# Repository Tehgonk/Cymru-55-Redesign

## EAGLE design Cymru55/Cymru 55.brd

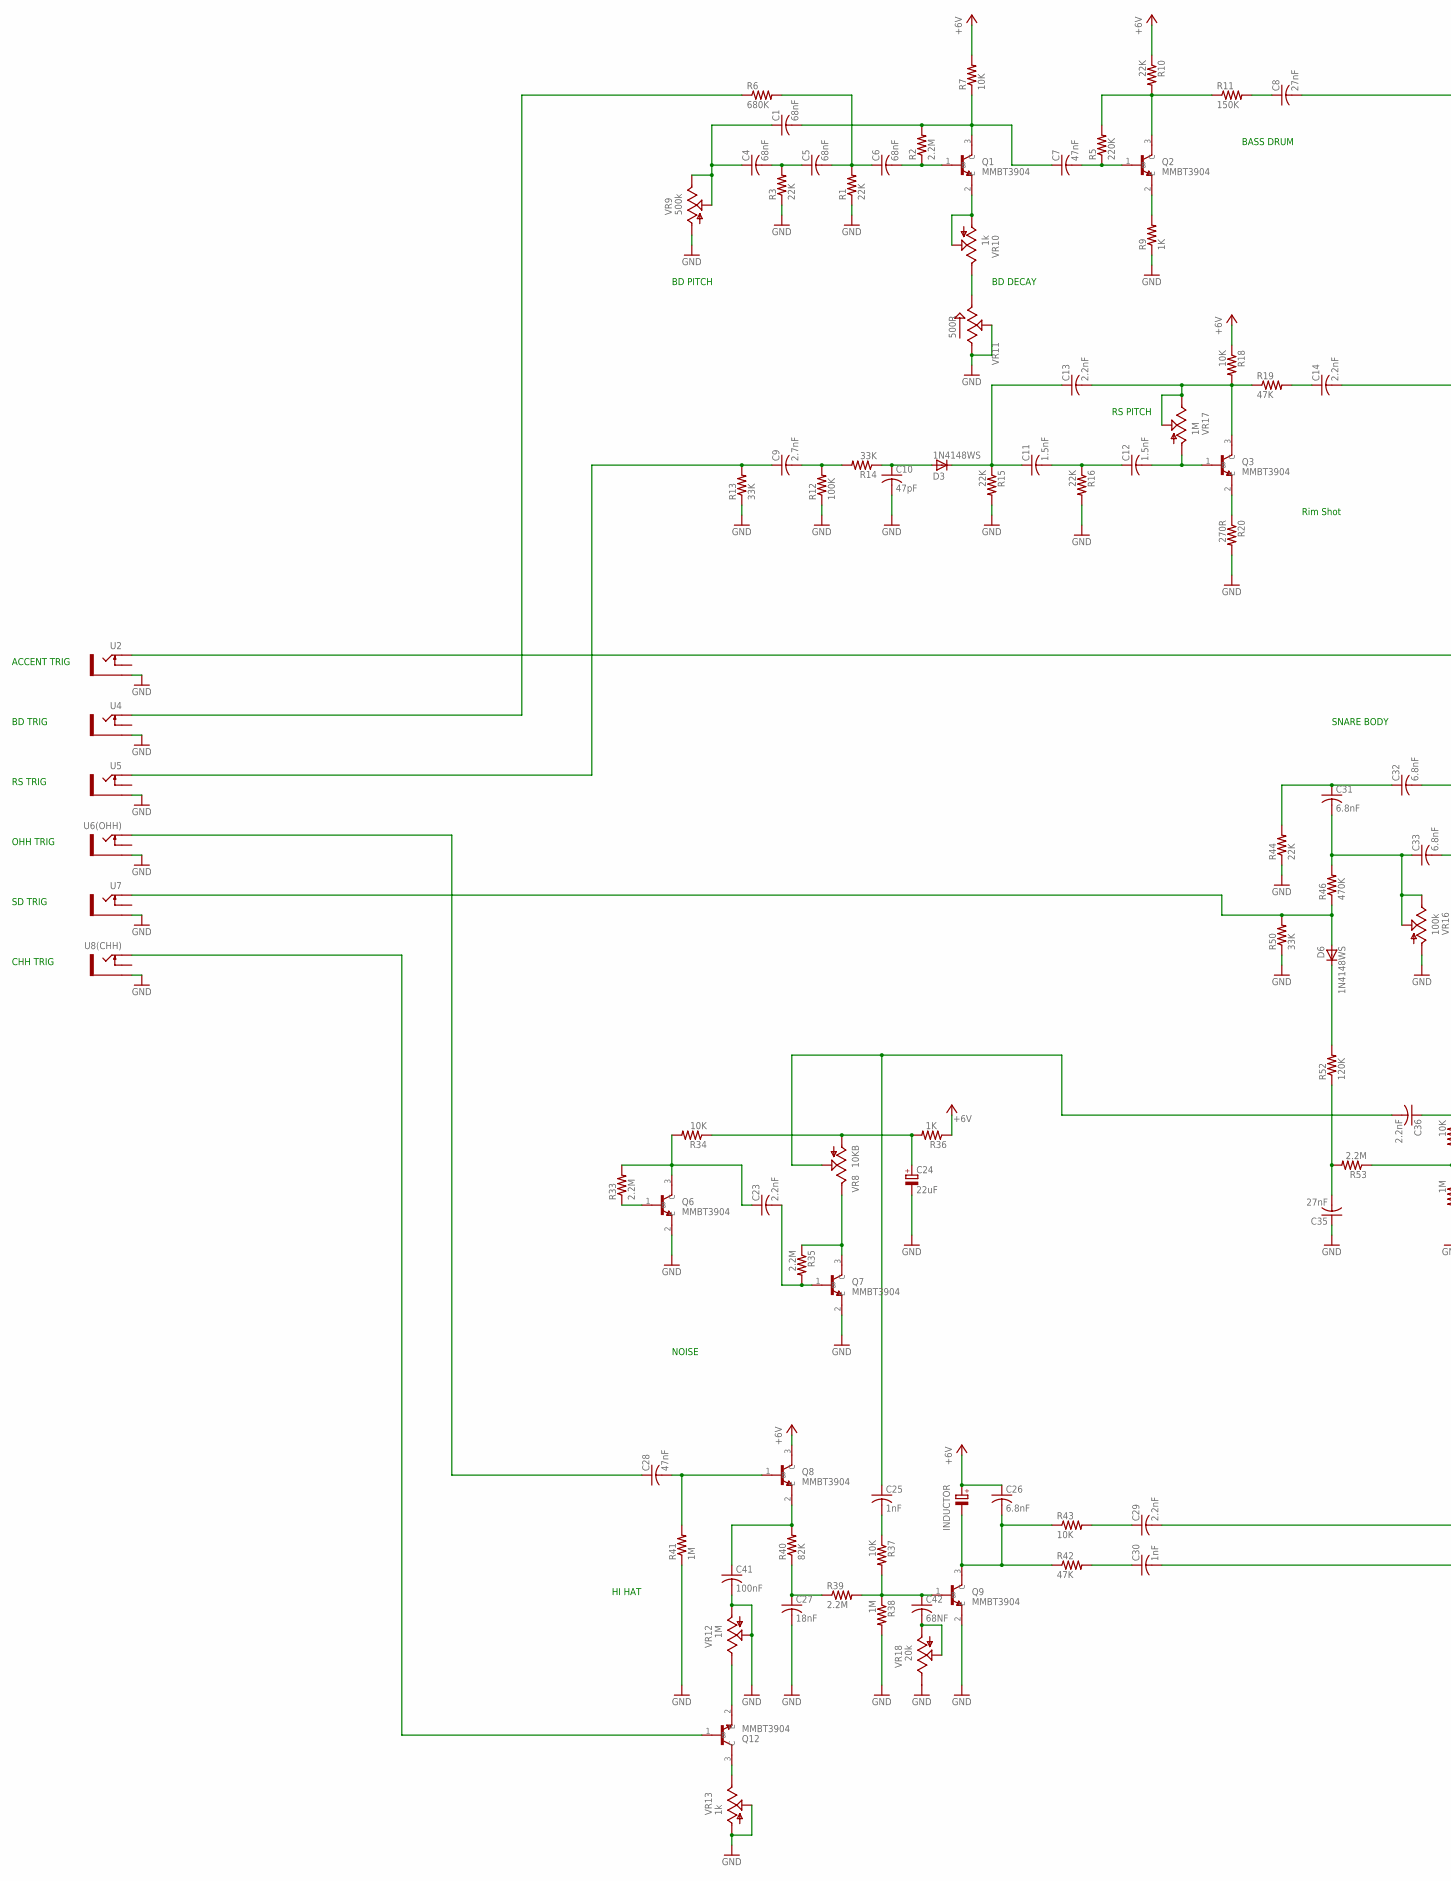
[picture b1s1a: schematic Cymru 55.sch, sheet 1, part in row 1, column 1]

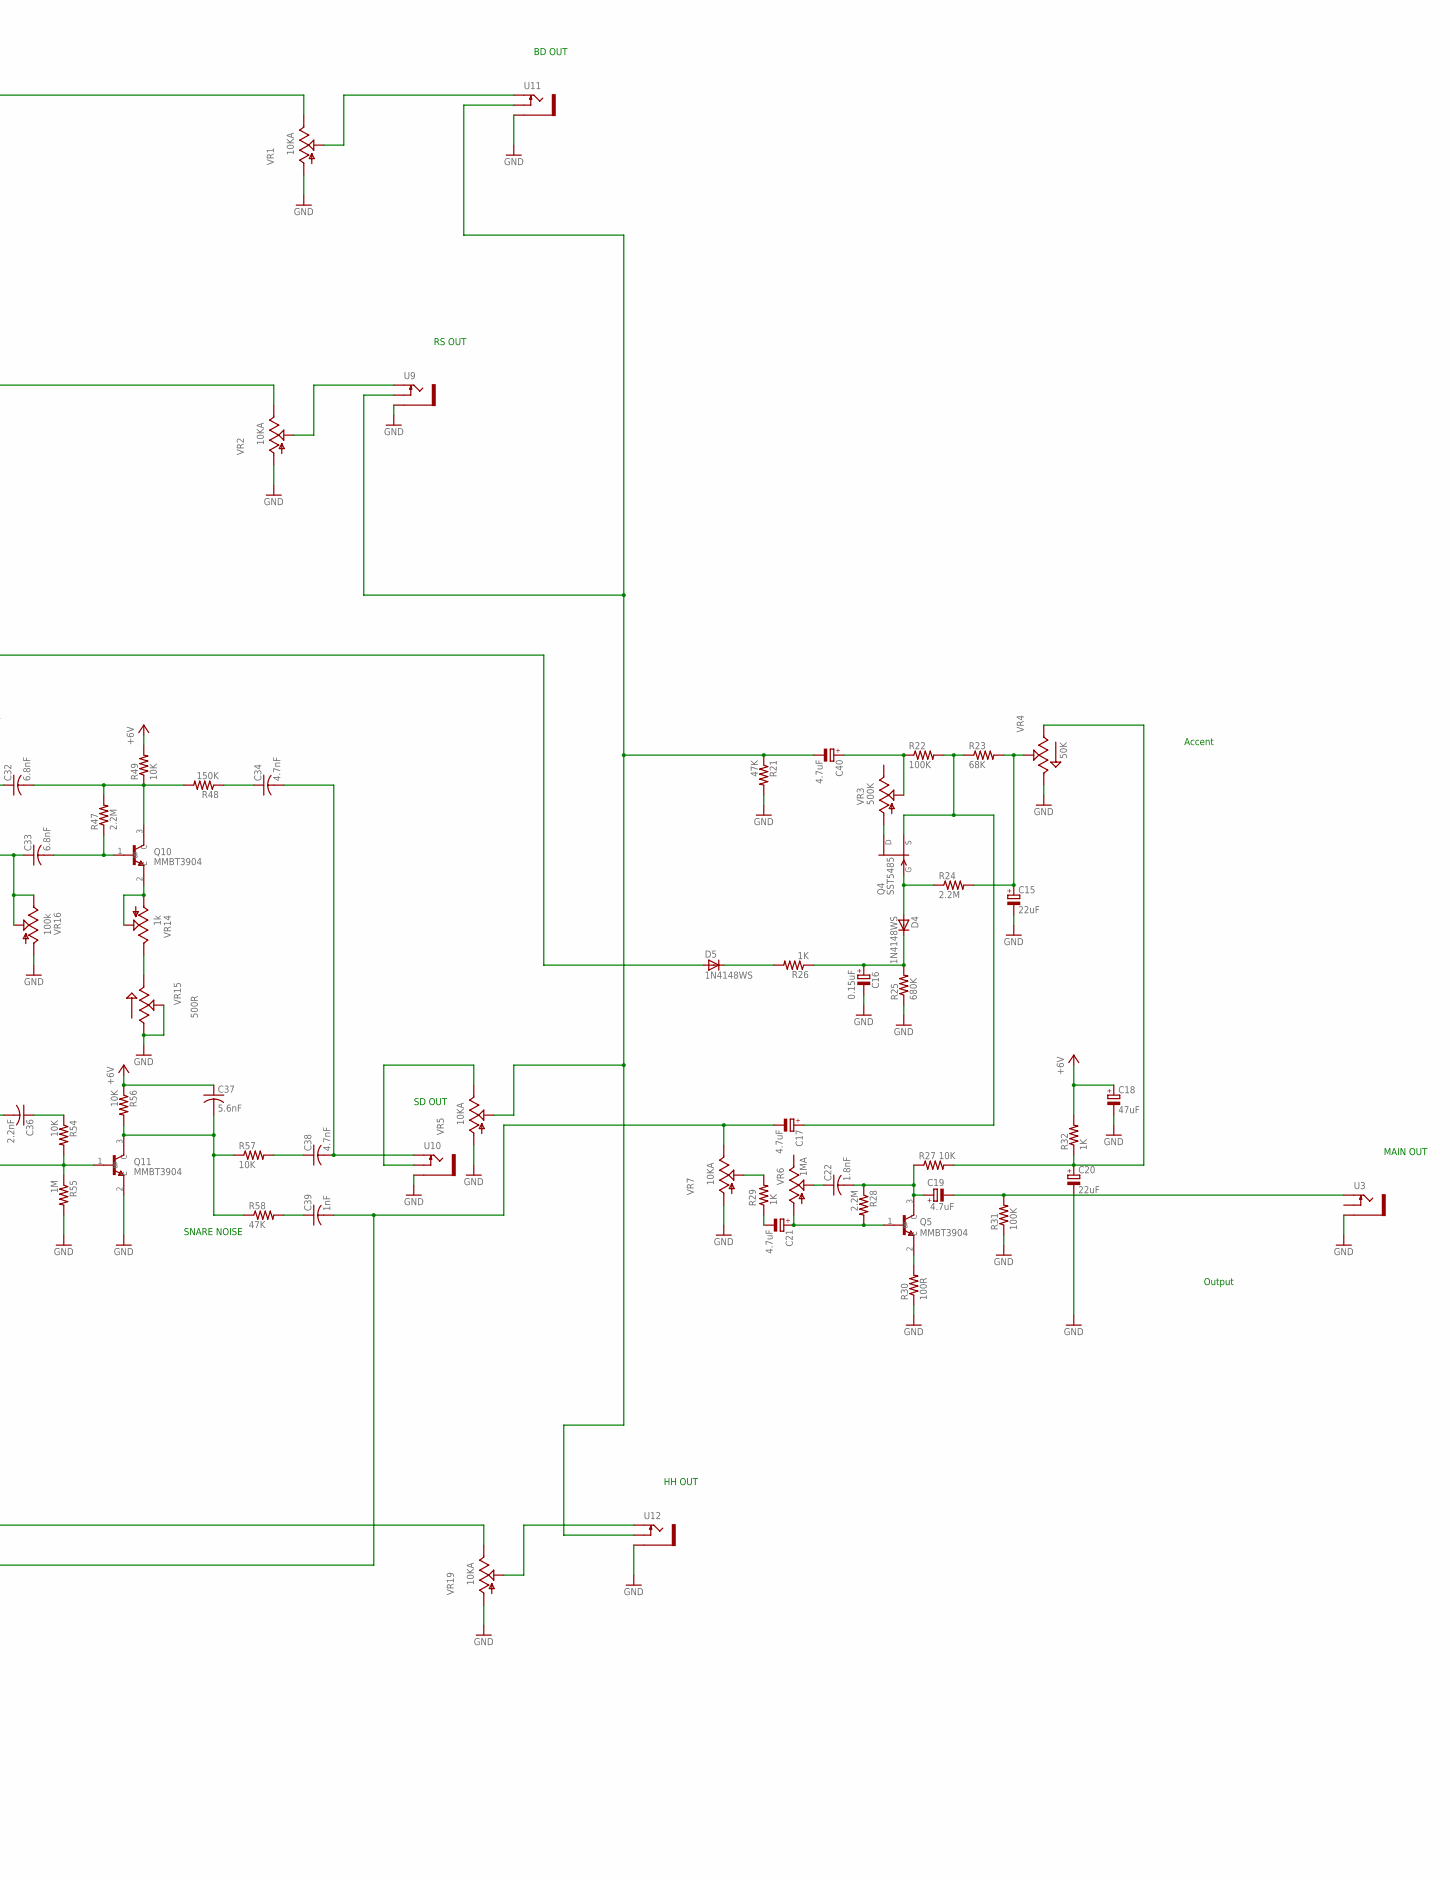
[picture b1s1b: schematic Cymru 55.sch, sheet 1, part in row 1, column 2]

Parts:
C1, C4, C5, C6: 68nF; C0603
C7, C28: 47nF; C0603
C8, C35: 27nF; C0603
C9: 2.7nF; C0603
C10: 47pF; C0603
C11, C12: 1.5nF; C0603
C13, C14, C23, C29, C36: 2.2nF; C0603
C15, C20, C24: 22uF; E2,5RE
C16: 0.15uF; E2,5RE
C17, C19, C21, C40: 4.7uF; E2,5RE
C18: 47uF; E2,5RE
C22: 1.8nF; C0603
C25, C30, C39: 1nF; C0603
C26, C31, C32, C33: 6.8nF; C0603
C27: 18nF; C0603
C34, C38: 4.7nF; C0603
C37: 5.6nF; C0603
C41: 100nF; C0603
C42: 68NF; C0603
D3, D4, D5, D6: 1N4148WS; SOD323
INDUCTOR: 47MH; E2,5RE
Q1, Q2, Q3, Q5, Q6, Q7, Q8, Q9, Q10, Q11, Q12: MMBT3904; SOT95P240X120-3N
Q4: SST5485; SOT23
R1, R3, R10, R15, R16, R44: 22K; R0603
R2, R24, R28, R33, R35, R39, R47, R53: 2.2M; R0603
R5: 220K; R0603
R6, R25: 680K; R0603
R7, R18, R27, R34, R37, R43, R49, R54, R56, R57: 10K; R0603
R9, R26, R29, R32, R36: 1K; R0603
R11, R48: 150K; R0603
R12, R22, R31: 100K; R0603
R13, R14, R50: 33K; R0603
R19, R21, R42, R58: 47K; R0603
R20: 270R; R0603
R23: 68K; R0603
R30: 100R; R0603
R38, R41, R55: 1M; R0603
R40: 82K; R0603
R46: 470K; R0603
R52: 120K; R0603
U2, U3, U4, U5, U6(OHH), U7, U8(CHH), U9, U10, U11, U12: THONKICONNNEW; WQP-PJ301M-12_JACK
VR1, VR2, VR5, VR7, VR19: 10KA; 9MM_SNAP-IN_POT
VR3: 500K; 9MM_SNAP-IN_POT
VR4: 50K; TRIM_3296W-1-250LF
VR6: 1MA; 9MM_SNAP-IN_POT
VR8: 10KB; 9MM_SNAP-IN_POT
VR9: 500k; 9MM_SNAP-IN_POT
VR10, VR13, VR14: 1k; 9MM_SNAP-IN_POT
VR11, VR15: 500R; TRIM_3296W-1-250LF
VR12, VR17: 1M; 9MM_SNAP-IN_POT
VR16: 100k; 9MM_SNAP-IN_POT
VR18: 20k; 9MM_SNAP-IN_POT

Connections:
+5V: C18.+, C26.1, C37.1, INDUCTOR.+, Q8.3 (C), R7.2, R10.1, R18.1, R32.2, R36.1, R49.2, R56.1; also elsewhere on the board
GND: C10.2, C15.-, C16.-, C18.-, C20.-, C24.-, C27.2, C35.1, C41.2, Q6.2 (E), Q7.2 (E), Q9.2 (E), Q11.2 (E), R1.1, R3.1, R9.1, R12.1, R13.1, R15.2, R16.2, R20.2, R21.2, R25.1, R30.1, R31.1, R38.2, R41.1, R44.1, R50.1, R55.2, U2.P$3_SLEEVE (SLEEVE), U3.P$3_SLEEVE (SLEEVE), U4.P$3_SLEEVE (SLEEVE), U5.P$3_SLEEVE (SLEEVE), U6(OHH).P$3_SLEEVE (SLEEVE), U7.P$3_SLEEVE (SLEEVE), U8(CHH).P$3_SLEEVE (SLEEVE), U9.P$3_SLEEVE (SLEEVE), U10.P$3_SLEEVE (SLEEVE), U11.P$3_SLEEVE (SLEEVE), U12.P$3_SLEEVE (SLEEVE), VR1.1 (A), VR2.1 (A), VR4.3 (CW), VR5.1 (A), VR7.1 (A), VR9.1 (A), VR11.1 (CCW), VR11.2 (WIPER), VR12.1 (A), VR12.2 (S), VR13.1 (A), VR13.2 (S), VR15.1 (CCW), VR15.2 (WIPER), VR16.1 (A), VR18.3 (E), VR19.1 (A); also elsewhere on the board
unnamed: U10.P$2_SWITCH (SWITCH), VR5.3 (E)
unnamed: C1.1, C4.1, VR9.2 (S), VR9.3 (E)
unnamed: C1.2, C7.1, Q1.3 (C), R2.2, R7.1
unnamed: C6.2, Q1.1 (B), R2.1
unnamed: C5.2, C6.1, R1.2, R6.2
unnamed: C4.2, C5.1, R3.2
unnamed: Q3.2 (E), R20.1
unnamed: C9.2, R12.2, R14.2
unnamed: Q1.2 (E), VR10.1 (A), VR10.2 (S)
unnamed: C10.1, D3.A, R14.1
unnamed: C7.2, Q2.1 (B), R5.1
unnamed: Q2.3 (C), R5.2, R10.2, R11.1
unnamed: Q2.2 (E), R9.2
unnamed: C8.1, R11.2
unnamed: C11.1, C13.1, D3.C, R15.1
unnamed: C11.2, C12.1, R16.1
unnamed: C9.1, R13.2, U5.P$1_TIP (TIP)
unnamed: D4.A, Q4.3 (G), R24.1
unnamed: C16.+, D4.C, R25.2, R26.1
unnamed: C12.2, Q3.1 (B), VR17.1 (A)
unnamed: C14.2, VR2.3 (E)
unnamed: C14.1, R19.2
unnamed: Q4.1 (D), VR3.1 (A)
unnamed: C40.+, R22.1, VR3.2 (S)
unnamed: C21.-, R29.1
unnamed: C17.-, C30.2, C39.2, VR7.3 (E)
unnamed: C15.+, R23.2, R24.2, VR4.2 (WIPER)
unnamed: C17.+, Q4.2 (S), R22.2, R23.1
unnamed: R29.2, VR7.2 (S)
unnamed: C21.+, Q5.1 (B), R28.2, VR6.1 (A)
unnamed: C22.1, VR6.2 (S)
unnamed: C19.-, R31.2, U3.P$1_TIP (TIP)
unnamed: Q6.1 (B), R33.1
unnamed: C20.+, R27.2, R32.1, VR4.1 (CCW)
unnamed: Q5.2 (E), R30.2
unnamed: C23.1, Q6.3 (C), R33.2, R34.2
unnamed: C25.1, C36.2, VR8.2 (S)
unnamed: C23.2, Q7.1 (B), R35.2
unnamed: Q7.3 (C), R35.1, VR8.3 (E)
unnamed: C24.+, R34.1, R36.2, VR8.1 (A)
unnamed: C25.2, R37.1
unnamed: C42.2, VR18.1 (A), VR18.2 (S)
unnamed: C27.1, R39.1, R40.1
unnamed: C41.1, Q8.2 (E), R40.2
unnamed: C26.2, INDUCTOR.-, Q9.3 (C), R42.1, R43.1
unnamed: C28.2, Q8.1 (B), R41.2
unnamed: C29.1, R43.2
unnamed: C30.1, R42.2
unnamed: D5.C, R26.2
unnamed: C31.1, C32.1, R44.2
unnamed: C13.2, Q3.3 (C), R18.2, R19.1, VR17.2 (S), VR17.3 (E)
unnamed: C32.2, Q10.3 (C), R47.2, R48.2, R49.1
unnamed: C34.1, R48.1
unnamed: C33.2, Q10.1 (B), R47.1
unnamed: C31.2, C33.1, R46.2, VR16.2 (S), VR16.3 (E)
unnamed: C8.2, VR1.3 (E)
unnamed: D6.C, R52.2
unnamed: C35.2, R52.1, R53.2
unnamed: Q11.1 (B), R53.1, R54.2, R55.1
unnamed: C36.1, R54.1
unnamed: C37.2, Q11.3 (C), R56.2, R57.1, R58.1
unnamed: R6.1, U4.P$1_TIP (TIP)
unnamed: C39.1, R58.2
unnamed: C38.1, R57.2
unnamed: D5.A, U2.P$1_TIP (TIP)
unnamed: C28.1, U6(OHH).P$1_TIP (TIP)
unnamed: D6.A, R46.1, R50.2, U7.P$1_TIP (TIP)
unnamed: VR10.3 (E), VR11.3 (CW)
unnamed: Q12.2 (E), VR12.3 (E)
unnamed: Q10.2 (E), VR14.1 (A), VR14.2 (S)
unnamed: Q12.3 (C), VR13.3 (E)
unnamed: Q12.1 (B), U8(CHH).P$1_TIP (TIP)
unnamed: VR14.3 (E), VR15.3 (CW)
unnamed: C34.2, C38.2, U10.P$1_TIP (TIP)
unnamed: U9.P$1_TIP (TIP), VR2.2 (S)
unnamed: C19.+, C22.2, Q5.3 (C), R27.1, R28.1
unnamed: C42.1, Q9.1 (B), R37.2, R38.1, R39.2
unnamed: U11.P$1_TIP (TIP), VR1.2 (S)
unnamed: C40.-, R21.1, U9.P$2_SWITCH (SWITCH), U11.P$2_SWITCH (SWITCH), U12.P$2_SWITCH (SWITCH), VR5.2 (S)
unnamed: C29.2, VR19.3 (E)
unnamed: U12.P$1_TIP (TIP), VR19.2 (S)

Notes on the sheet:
BASS DRUM
Rim Shot
Accent
Output
SNARE BODY
HI HAT
NOISE
SNARE NOISE
SD TRIG
OHH TRIG
RS TRIG
ACCENT TRIG
BD TRIG
CHH TRIG
BD OUT
RS OUT
SD OUT
HH OUT
MAIN OUT
BD PITCH
BD DECAY
RS PITCH

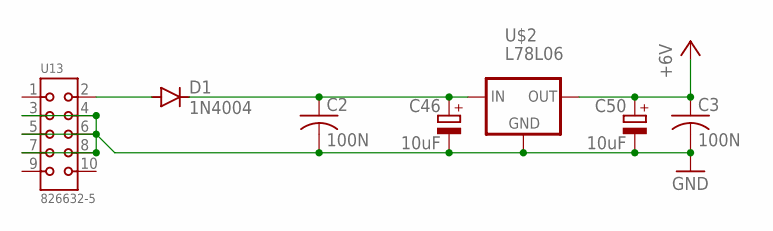
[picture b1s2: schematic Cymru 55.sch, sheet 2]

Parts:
C2, C3: 100N; C0603
C46, C50: 10uF; E2,5RE
D1: 1N4004; DO41-10
U13: 826632-5; HDRV10W63P254_2X5_1270X500X950P
U$2: L78L06; SOT89

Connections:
+5V: C3.1, C50.+, U$2.1 (OUT); also elsewhere on the board
GND: C2.2, C3.2, C46.-, C50.-, U13.3, U13.4, U13.5, U13.6, U13.7, U13.8, U$2.2 (GND); also elsewhere on the board
unnamed: C2.1, C46.+, D1.C, U$2.3 (IN)
unnamed: D1.A, U13.2

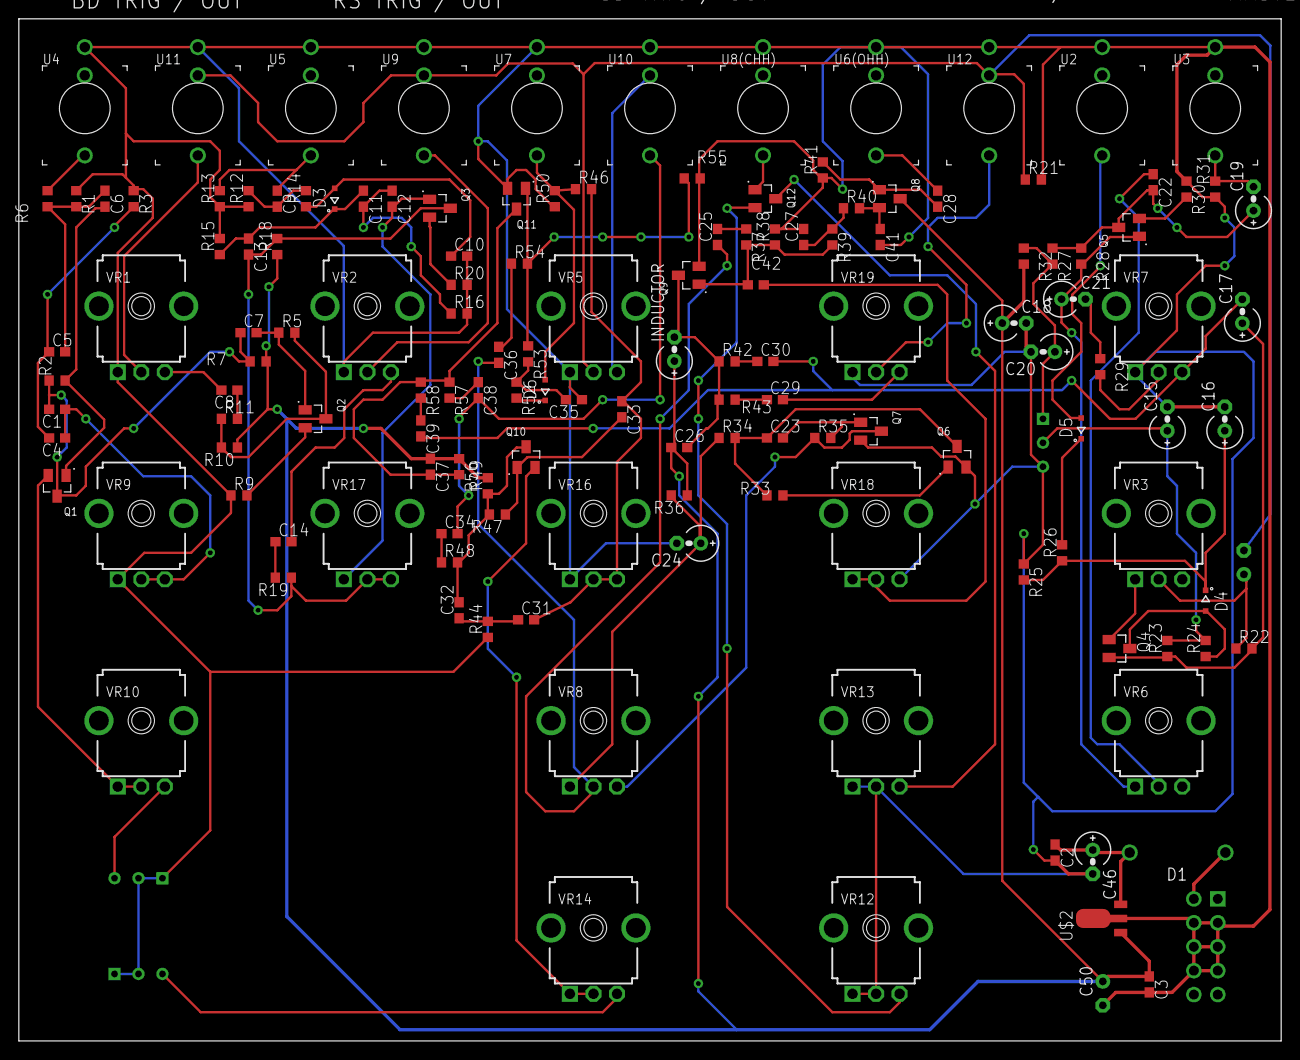
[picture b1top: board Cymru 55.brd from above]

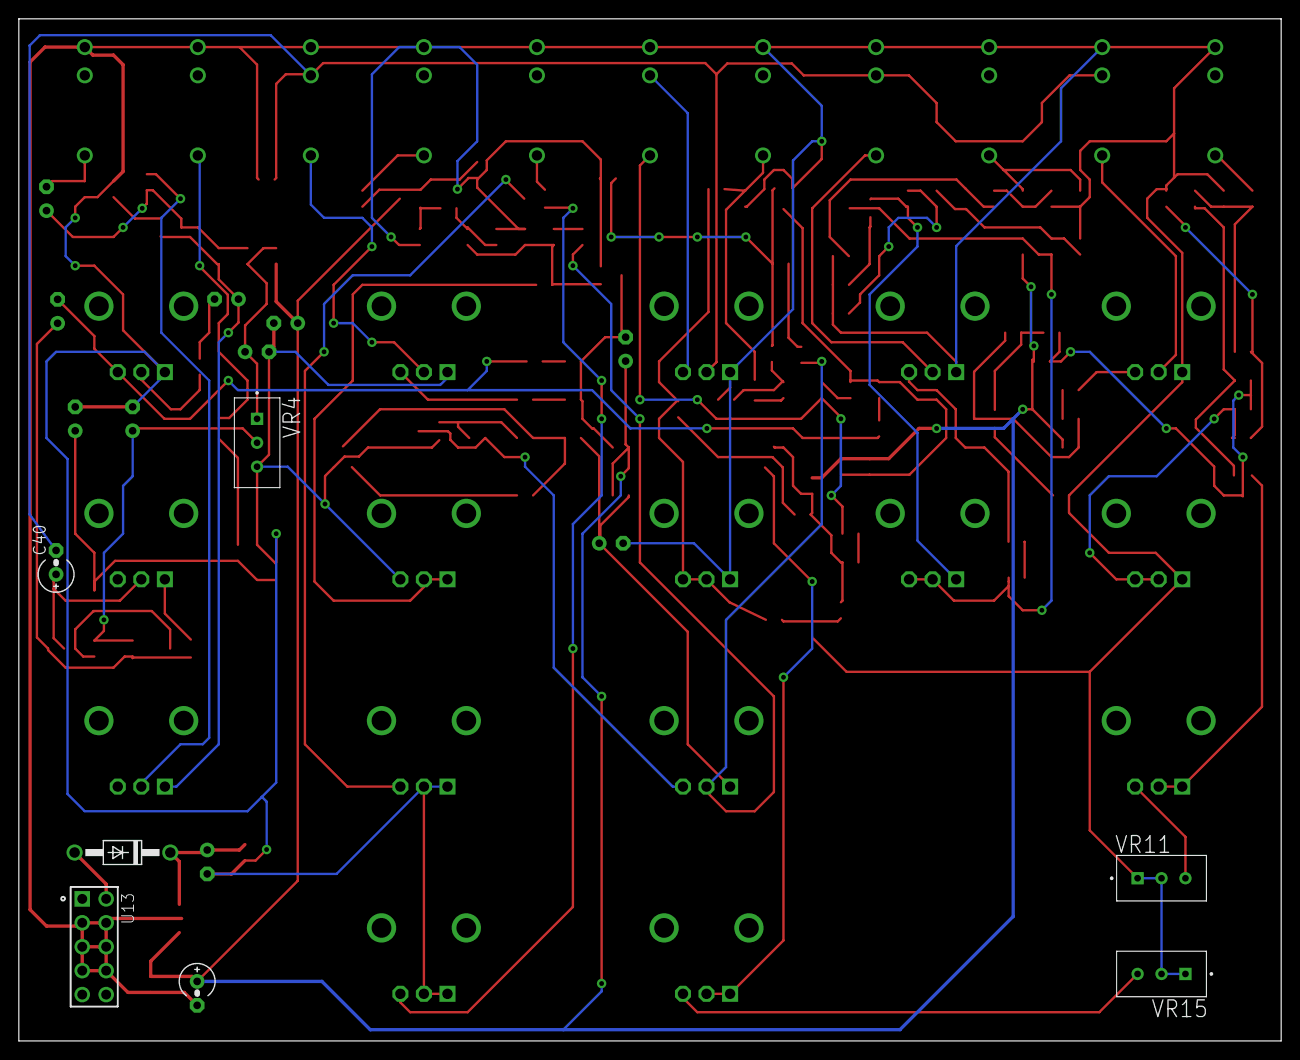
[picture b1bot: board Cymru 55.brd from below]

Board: 2 copper layers, 134.0 x 108.5 mm, 147 parts (7 on the bottom side), 85 nets.
